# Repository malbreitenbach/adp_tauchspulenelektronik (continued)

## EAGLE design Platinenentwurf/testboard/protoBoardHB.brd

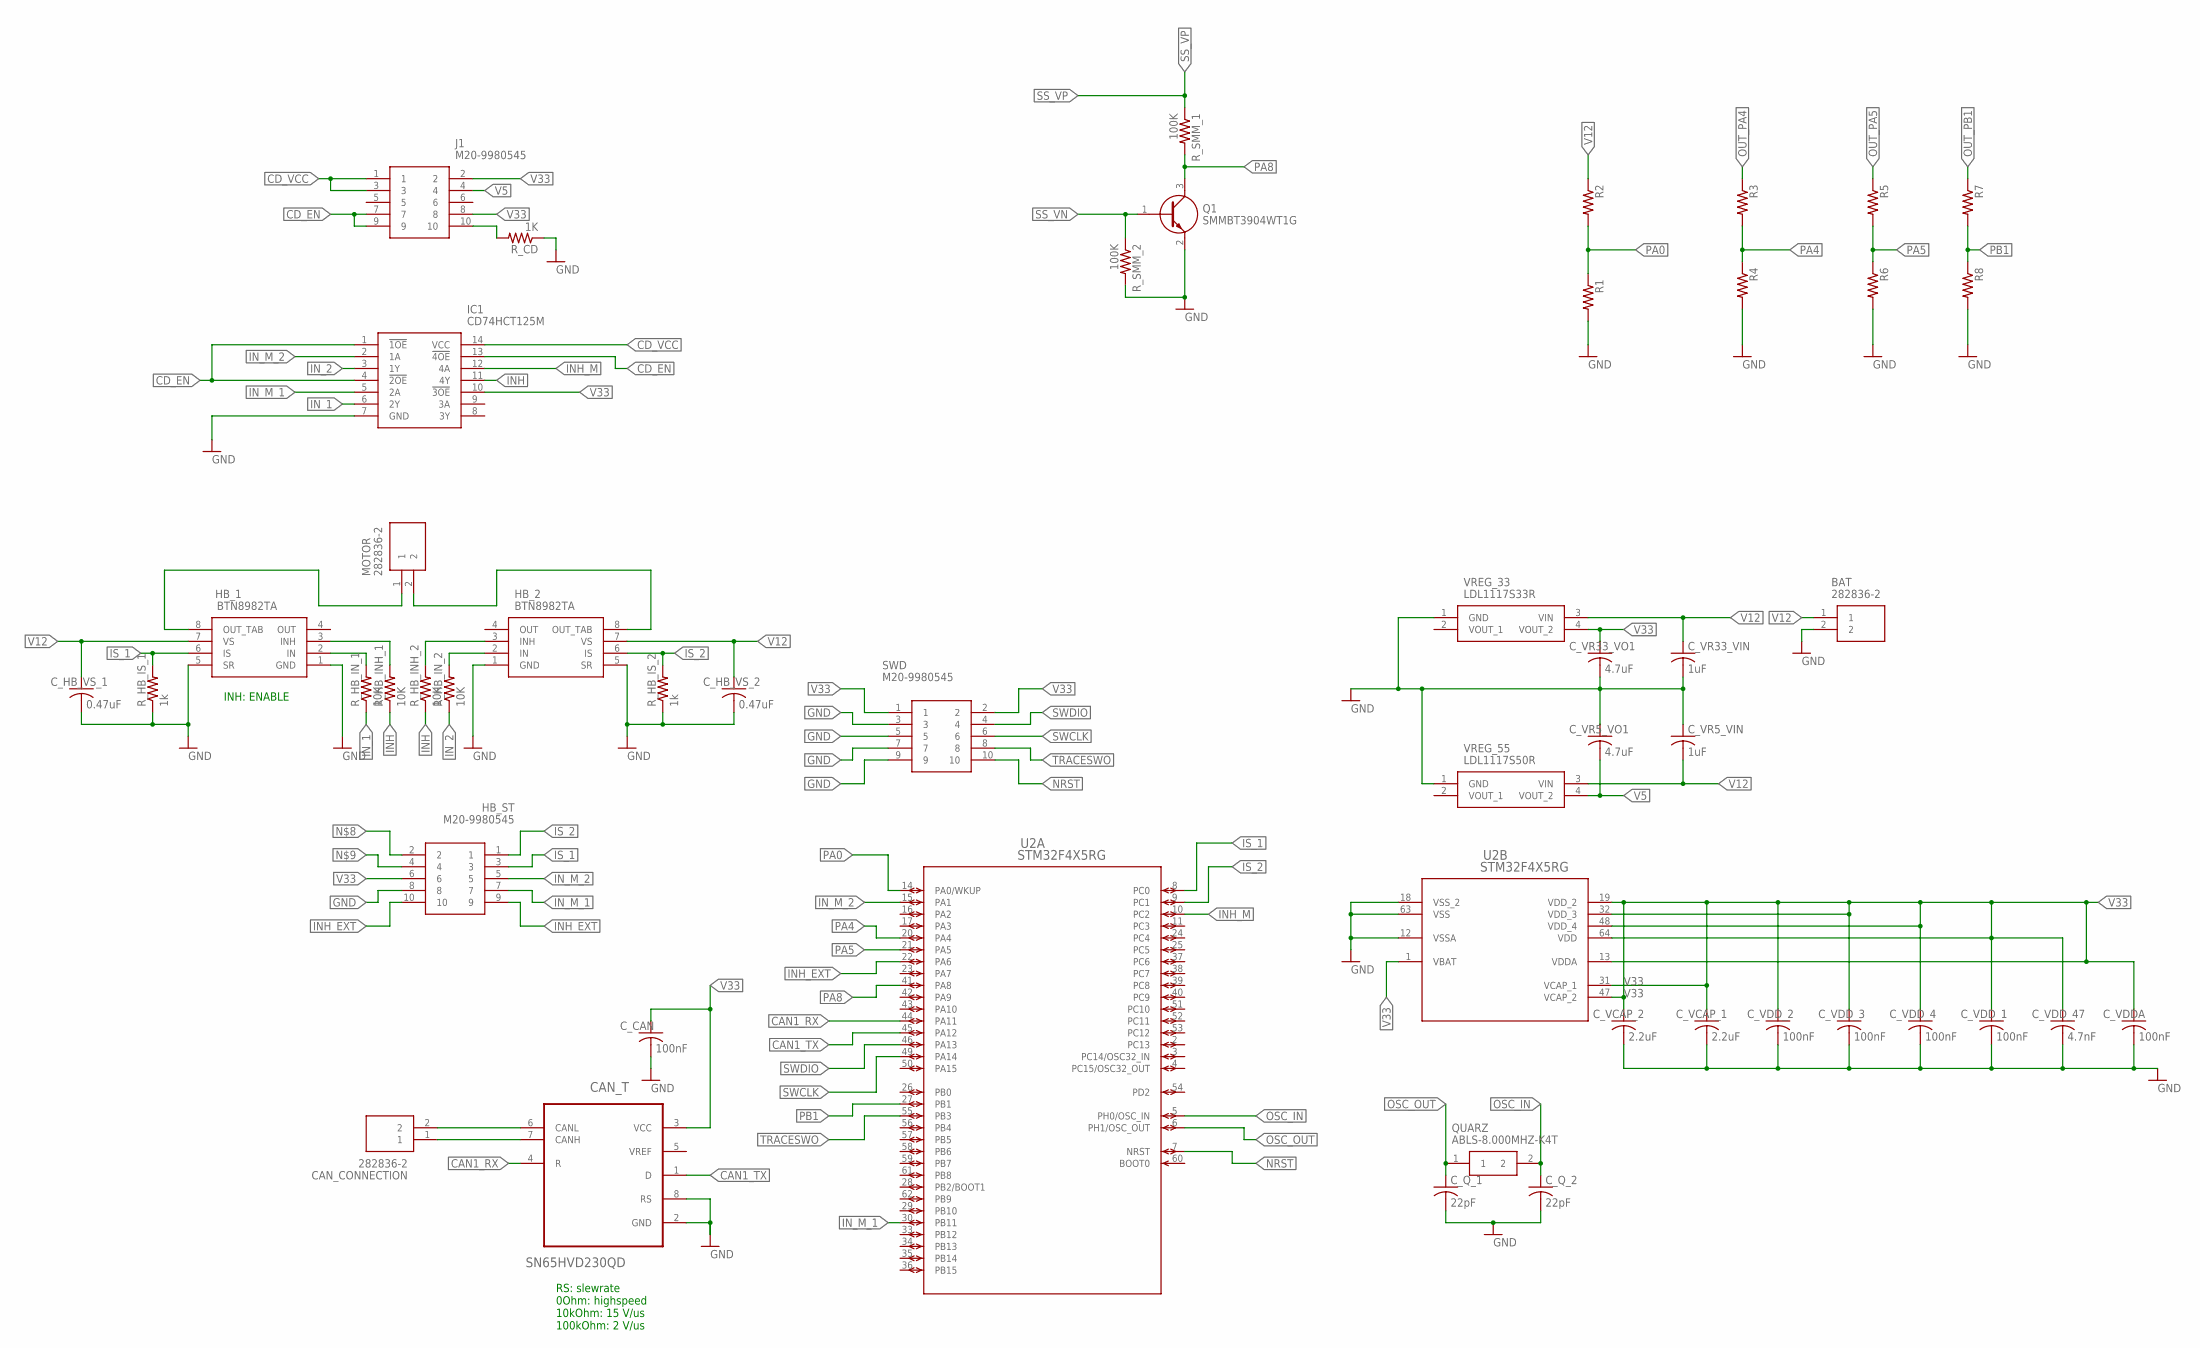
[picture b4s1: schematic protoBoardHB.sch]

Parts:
BAT: 282836-2; SHDR2W100P0X500_1X2_1000X820X1
CAN_CONNECTION: 282836-2; SHDR2W100P0X500_1X2_1000X820X1
CAN_T: SN65HVD230QD; SOIC127P600X175-8N; MPN SN65HVD230QD..
C_CAN: 100nF; C1206
C_HB_VS_1, C_HB_VS_2: 0.47uF; C1206
C_Q_1, C_Q_2: 22pF; C0805
C_VCAP_1, C_VCAP_2: 2.2uF; C1206
C_VDDA: 100nF; C1206
C_VDD_1, C_VDD_2, C_VDD_3, C_VDD_4: 100nF; C1206
C_VDD_47: 4.7nF; C1206
C_VR5_VIN, C_VR33_VIN: 1uF; C1206
C_VR5_VO1, C_VR33_VO1: 4.7uF; C1206
HB_1, HB_2: BTN8982TA; TO127P1500X440-8N
HB_ST: M20-9980545; HDRV10W80P254_2X5_1270X508X864; MPN M20-9980545
IC1: CD74HCT125M; SOIC127P600X175-14N
J1: M20-9980545; HDRV10W80P254_2X5_1270X508X864
MOTOR: 282836-2; SHDR2W100P0X500_1X2_1000X820X1
Q1: SMMBT3904WT1G; SOT65P220X100-3N
QUARZ: ABLS-8.000MHZ-K4T; ABLS-12.000MHZ-B2; MPN ABLS-8.000MHZ-K4T
R1, R2, R3, R4, R5, R6, R7, R8: R-US_R1206; R1206
R_CD: 1K; R1206
R_HB_INH_1, R_HB_INH_2: 10K; R1206
R_HB_IN_1, R_HB_IN_2: 10K; R1206
R_HB_IS_1, R_HB_IS_2: 1k; R1206
R_SMM_1, R_SMM_2: 100K; R1206
SWD: M20-9980545; HDRV10W80P254_2X5_1270X508X864; MPN M20-9980545
U2: STM32F4X5RG; LQFP64-10X10MM
VREG_33: LDL1117S33R; SOT230P700X180-4N; MPN LDL1117S33R
VREG_55: LDL1117S50R; SOT230P700X180-4N; MPN LDL1117S50R

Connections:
CAN1_RX: CAN_T.4 (R), U2.44 (PA11)
CAN1_TX: CAN_T.1 (D), U2.45 (PA12)
CANH: CAN_CONNECTION.1, CAN_T.7 (CANH)
CANL: CAN_CONNECTION.2, CAN_T.6 (CANL)
CD_EN: IC1.1 (!1OE), IC1.4 (!2OE), IC1.13 (!4OE), J1.7, J1.9
CD_VCC: IC1.14 (VCC), J1.1, J1.3
GND: BAT.2, CAN_T.2 (GND), CAN_T.8 (RS), C_CAN.2, C_HB_VS_1.2, C_HB_VS_2.2, C_Q_1.2, C_Q_2.2, C_VCAP_1.2, C_VCAP_2.2, C_VDDA.2, C_VDD_1.2, C_VDD_2.2, C_VDD_3.2, C_VDD_4.2, C_VDD_47.2, C_VR5_VIN.1, C_VR5_VO1.1, C_VR33_VIN.2, C_VR33_VO1.2, HB_1.1 (GND), HB_1.5 (SR), HB_2.1 (GND), HB_2.5 (SR), HB_ST.8, IC1.7 (GND), Q1.2 (E), R1.2, R4.2, R6.2, R8.2, R_CD.1, R_HB_IS_1.1, R_HB_IS_2.1, R_SMM_2.2, SWD.3, SWD.5, SWD.7, SWD.9, U2.12 (VSSA), U2.18 (VSS_2), U2.63 (VSS), VREG_33.1 (GND), VREG_55.1 (GND)
INH: IC1.11 (4Y), R_HB_INH_1.1, R_HB_INH_2.1
INH_EXT: HB_ST.9, HB_ST.10, U2.22 (PA6)
INH_M: IC1.12 (4A), U2.10 (PC2)
IN_1: IC1.6 (2Y), R_HB_IN_1.1
IN_2: IC1.3 (1Y), R_HB_IN_2.1
IN_M_1: HB_ST.7, IC1.5 (2A), U2.30 (PB11)
IN_M_2: HB_ST.5, IC1.2 (1A), U2.15 (PA1)
IS_1: HB_1.6 (IS), HB_ST.3, R_HB_IS_1.2, U2.8 (PC0)
IS_2: HB_2.6 (IS), HB_ST.1, R_HB_IS_2.2, U2.9 (PC1)
unnamed: J1.10, R_CD.2
unnamed: HB_1.2 (IN), R_HB_IN_1.2
unnamed: HB_1.3 (INH), R_HB_INH_1.2
unnamed: HB_2.2 (IN), R_HB_IN_2.2
unnamed: HB_2.3 (INH), R_HB_INH_2.2
NRST: SWD.10, U2.7 (NRST)
OSC_IN: C_Q_2.1, QUARZ.2, U2.5 (PH0/OSC_IN)
OSC_OUT: C_Q_1.1, QUARZ.1, U2.6 (PH1/OSC_OUT)
OUT_PA4: R3.1
OUT_PA5: R5.1
OUT_PB1: R7.1
PA0: R1.1, R2.2, U2.14 (PA0/WKUP)
PA4: R3.2, R4.1, U2.20 (PA4)
PA5: R5.2, R6.1, U2.21 (PA5)
PA8: Q1.3 (C), R_SMM_1.2, U2.41 (PA8)
PB1: R7.2, R8.1, U2.27 (PB1)
SS_VN: Q1.1 (B), R_SMM_2.1
SS_VP: R_SMM_1.1
SWCLK: SWD.6, U2.49 (PA14)
SWDIO: SWD.4, U2.46 (PA13)
TRACESWO: SWD.8, U2.55 (PB3)
V5: C_VR5_VO1.2, J1.4, VREG_55.4 (VOUT_2)
V12: BAT.1, C_HB_VS_1.1, C_HB_VS_2.1, C_VR5_VIN.2, C_VR33_VIN.1, HB_1.7 (VS), HB_2.7 (VS), R2.1, VREG_33.3 (VIN), VREG_55.3 (VIN)
V33: CAN_T.3 (VCC), C_CAN.1, C_VCAP_1.1, C_VCAP_2.1, C_VDDA.1, C_VDD_1.1, C_VDD_2.1, C_VDD_3.1, C_VDD_4.1, C_VDD_47.1, C_VR33_VO1.1, HB_ST.6, IC1.10 (!3OE), J1.2, J1.8, SWD.1, SWD.2, U2.1 (VBAT), U2.13 (VDDA), U2.19 (VDD_2), U2.31 (VCAP_1), U2.32 (VDD_3), U2.47 (VCAP_2), U2.48 (VDD_4), U2.64 (VDD), VREG_33.4 (VOUT_2)
V_MOT_MIN: HB_2.8 (OUT_TAB), MOTOR.2
V_MOT_PL: HB_1.8 (OUT_TAB), MOTOR.1

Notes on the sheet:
RS: slewrate 0Ohm: highspeed 10kOhm: 15 V/us 100kOhm: 2 V/us
INH: ENABLE

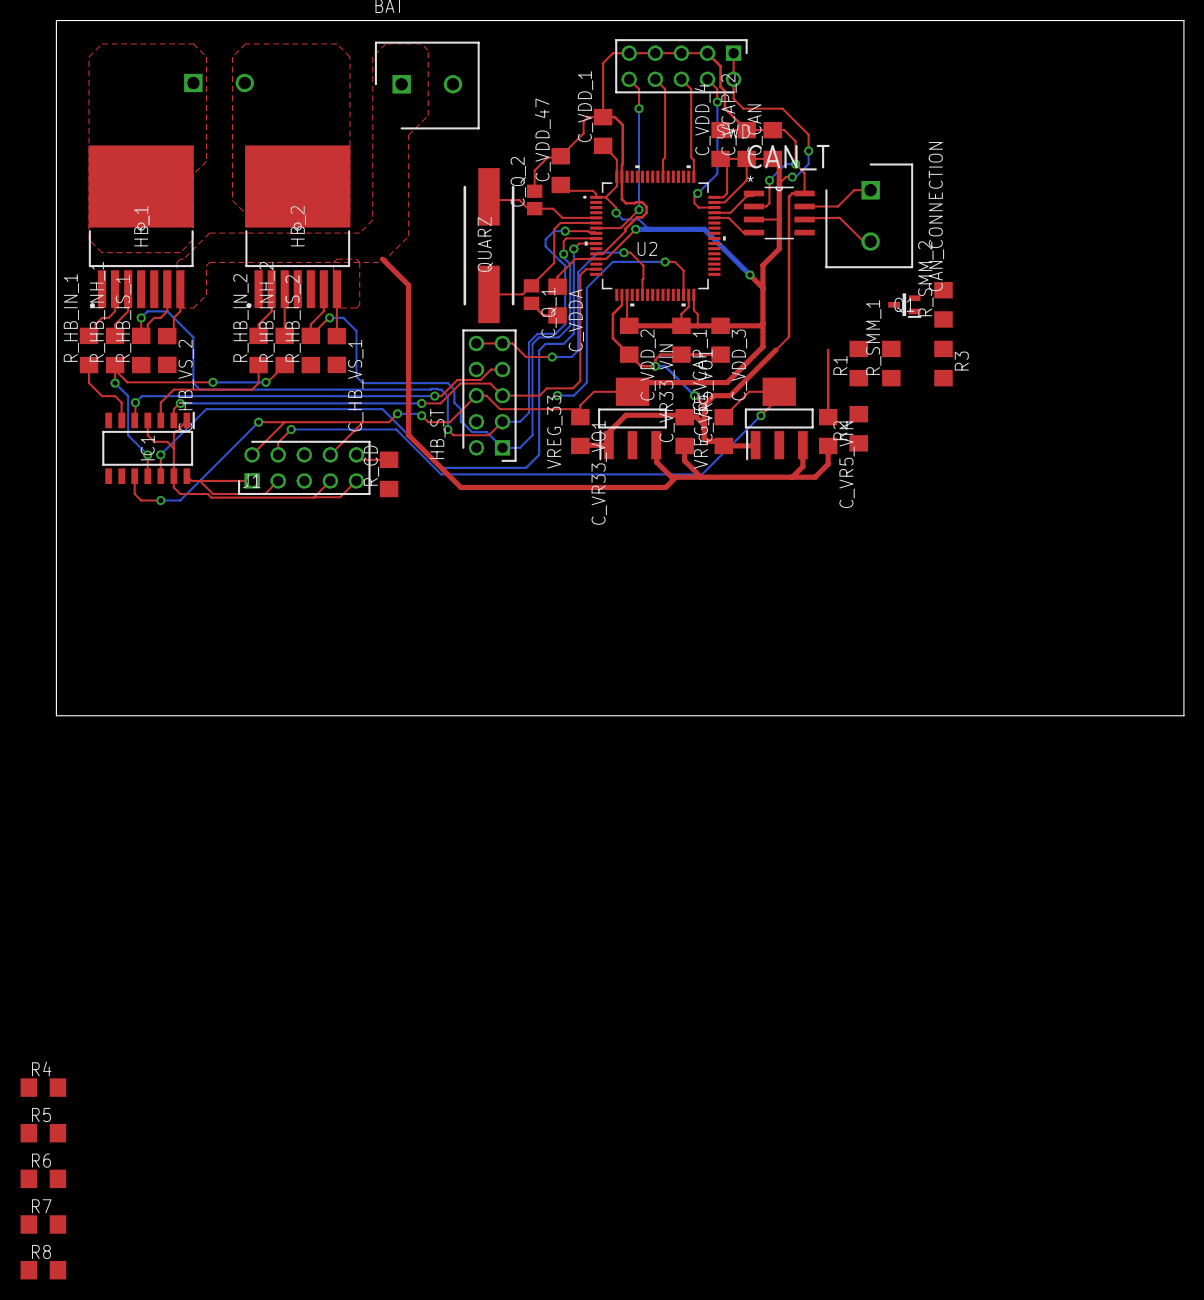
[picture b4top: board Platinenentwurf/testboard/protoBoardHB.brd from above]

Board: 2 copper layers, 109.8 x 67.7 mm, 49 parts (1 on the bottom side), 38 nets.

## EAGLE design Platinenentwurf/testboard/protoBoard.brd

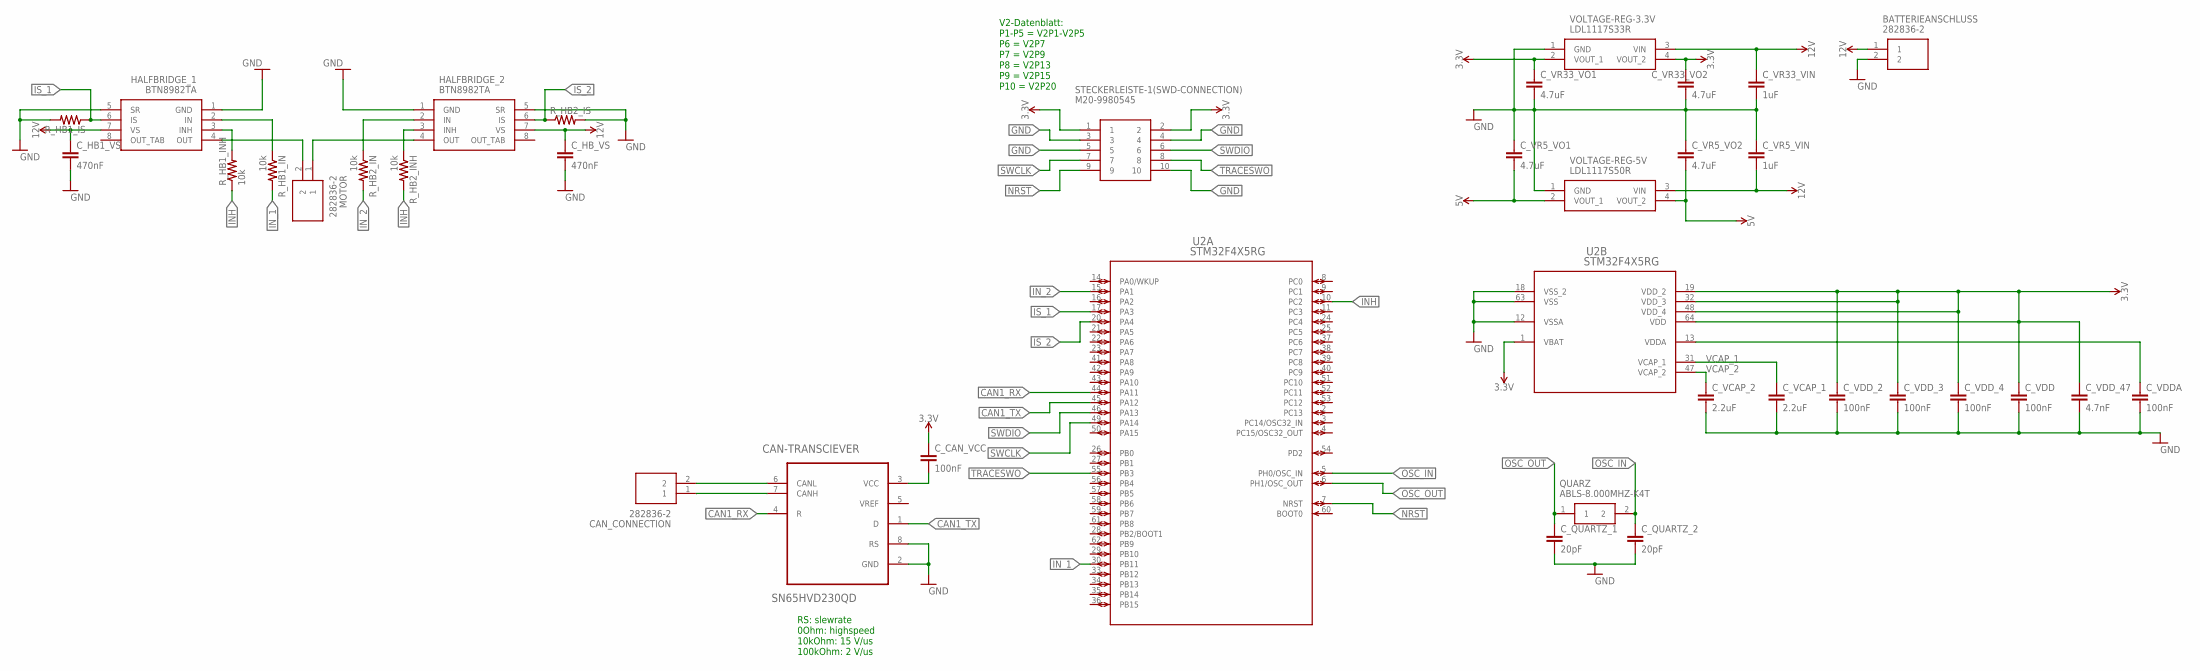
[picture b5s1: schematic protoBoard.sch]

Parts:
BATTERIEANSCHLUSS: 282836-2; SHDR2W100P0X500_1X2_1000X820X1
CAN-TRANSCIEVER: SN65HVD230QD; SOIC127P600X175-8N; MPN SN65HVD230QD..
CAN_CONNECTION: 282836-2; SHDR2W100P0X500_1X2_1000X820X1
C_CAN_VCC: 100nF; C2.5-6
C_HB1_VS: 470nF; C2.5-6
C_HB_VS: 470nF; C2.5-6
C_QUARTZ_1, C_QUARTZ_2: 20pF; C2.5-6
C_VCAP_1, C_VCAP_2: 2.2uF; C2.5-6
C_VDD: 100nF; C2.5-6
C_VDDA: 100nF; C2.5-6
C_VDD_2, C_VDD_3, C_VDD_4: 100nF; C2.5-6
C_VDD_47: 4.7nF; C2.5-6
C_VR5_VIN, C_VR33_VIN: 1uF; C2.5-6
C_VR5_VO1, C_VR5_VO2, C_VR33_VO1, C_VR33_VO2: 4.7uF; C2.5-6
HALFBRIDGE_1, HALFBRIDGE_2: BTN8982TA; TO127P1500X440-8N
MOTOR: 282836-2; SHDR2W100P0X500_1X2_1000X820X1
QUARZ: ABLS-8.000MHZ-K4T; ABLS-12.000MHZ-B2; MPN ABLS-8.000MHZ-K4T
R_HB1_IN, R_HB1_INH, R_HB2_IN, R_HB2_INH: 10k; 0204/7
R_HB1_IS, R_HB2_IS: R-US_0204/7; 0204/7
STECKERLEISTE-1(SWD-CONNECTION): M20-9980545; HDRV10W80P254_2X5_1270X508X864; MPN M20-9980545
U2: STM32F4X5RG; LQFP64-10X10MM
VOLTAGE-REG-3.3V: LDL1117S33R; SOT230P700X180-4N; MPN LDL1117S33R
VOLTAGE-REG-5V: LDL1117S50R; SOT230P700X180-4N; MPN LDL1117S50R

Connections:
12V: BATTERIEANSCHLUSS.1, C_HB1_VS.1, C_HB_VS.1, C_VR5_VIN.2, C_VR33_VIN.1, HALFBRIDGE_1.7 (VS), HALFBRIDGE_2.7 (VS), VOLTAGE-REG-3.3V.3 (VIN), VOLTAGE-REG-5V.3 (VIN)
CAN1_RX: CAN-TRANSCIEVER.4 (R), U2.44 (PA11)
CAN1_TX: CAN-TRANSCIEVER.1 (D), U2.45 (PA12)
GND: BATTERIEANSCHLUSS.2, CAN-TRANSCIEVER.2 (GND), CAN-TRANSCIEVER.8 (RS), C_HB1_VS.2, C_HB_VS.2, C_QUARTZ_1.2, C_QUARTZ_2.2, C_VCAP_1.2, C_VCAP_2.2, C_VDD.2, C_VDDA.2, C_VDD_2.2, C_VDD_3.2, C_VDD_4.2, C_VDD_47.2, C_VR5_VIN.1, C_VR5_VO1.1, C_VR5_VO2.1, C_VR33_VIN.2, C_VR33_VO1.2, C_VR33_VO2.2, HALFBRIDGE_1.1 (GND), HALFBRIDGE_1.5 (SR), HALFBRIDGE_2.1 (GND), HALFBRIDGE_2.5 (SR), R_HB1_IS.2, R_HB2_IS.2, STECKERLEISTE-1(SWD-CONNECTION).3, STECKERLEISTE-1(SWD-CONNECTION).4, STECKERLEISTE-1(SWD-CONNECTION).5, STECKERLEISTE-1(SWD-CONNECTION).10, U2.12 (VSSA), U2.18 (VSS_2), U2.63 (VSS), VOLTAGE-REG-3.3V.1 (GND), VOLTAGE-REG-5V.1 (GND)
INH: R_HB1_INH.1, R_HB2_INH.2, U2.10 (PC2)
IN_1: R_HB1_IN.2, U2.30 (PB11)
IN_2: R_HB2_IN.2, U2.15 (PA1)
IS_1: HALFBRIDGE_1.6 (IS), R_HB1_IS.1, U2.17 (PA3)
IS_2: HALFBRIDGE_2.6 (IS), R_HB2_IS.1, U2.20 (PA4)
unnamed: C_VDDA.1, U2.13 (VDDA)
unnamed: CAN-TRANSCIEVER.3 (VCC), C_CAN_VCC.2
unnamed: CAN-TRANSCIEVER.6 (CANL), CAN_CONNECTION.2
unnamed: CAN-TRANSCIEVER.7 (CANH), CAN_CONNECTION.1
unnamed: HALFBRIDGE_1.4 (OUT), MOTOR.2
unnamed: HALFBRIDGE_2.4 (OUT), MOTOR.1
unnamed: HALFBRIDGE_1.3 (INH), R_HB1_INH.2
unnamed: HALFBRIDGE_2.3 (INH), R_HB2_INH.1
unnamed: HALFBRIDGE_1.2 (IN), R_HB1_IN.1
unnamed: HALFBRIDGE_2.2 (IN), R_HB2_IN.1
NRST: STECKERLEISTE-1(SWD-CONNECTION).9, U2.7 (NRST)
OSC_IN: C_QUARTZ_2.1, QUARZ.2, U2.5 (PH0/OSC_IN)
OSC_OUT: C_QUARTZ_1.1, QUARZ.1, U2.6 (PH1/OSC_OUT)
SWCLK: STECKERLEISTE-1(SWD-CONNECTION).7, U2.49 (PA14)
SWDIO: STECKERLEISTE-1(SWD-CONNECTION).6, U2.46 (PA13)
TRACESWO: STECKERLEISTE-1(SWD-CONNECTION).8, U2.55 (PB3)
VCAP_1: C_VCAP_1.1, U2.31 (VCAP_1)
VCAP_2: C_VCAP_2.1, U2.47 (VCAP_2)
VCC: C_CAN_VCC.1, C_VDD.1, C_VDD_2.1, C_VDD_3.1, C_VDD_4.1, C_VDD_47.1, C_VR5_VO1.2, C_VR5_VO2.2, C_VR33_VO1.1, C_VR33_VO2.1, STECKERLEISTE-1(SWD-CONNECTION).1, STECKERLEISTE-1(SWD-CONNECTION).2, U2.1 (VBAT), U2.19 (VDD_2), U2.32 (VDD_3), U2.48 (VDD_4), U2.64 (VDD), VOLTAGE-REG-3.3V.2 (VOUT_1), VOLTAGE-REG-3.3V.4 (VOUT_2), VOLTAGE-REG-5V.2 (VOUT_1), VOLTAGE-REG-5V.4 (VOUT_2)

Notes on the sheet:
RS: slewrate 0Ohm: highspeed 10kOhm: 15 V/us 100kOhm: 2 V/us
V2-Datenblatt: P1-P5 = V2P1-V2P5 P6 = V2P7 P7 = V2P9 P8 = V2P13 P9 = V2P15 P10 = V2P20

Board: 2 copper layers, 36 parts (0 on the bottom side), 28 nets, no tracks yet.

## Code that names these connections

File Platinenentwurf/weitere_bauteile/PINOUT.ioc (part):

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Mcu.Name=STM32F405RGTx
Mcu.Package=LQFP64
Mcu.UserName=STM32F405RGTx
PA0-WKUP.Signal=ADCx_IN0
PA1.Signal=ADCx_IN1
PA11.Mode=Master
PA11.Signal=CAN1_RX
PA12.Mode=Master
PA12.Signal=CAN1_TX
PA13.Mode=Serial_Wire
PA13.Signal=SYS_JTMS-SWDIO
PA14.Mode=Serial_Wire
PA14.Signal=SYS_JTCK-SWCLK
PA2.Mode=Asynchronous
PA2.Signal=USART2_TX
PA3.Mode=Asynchronous
PA3.Signal=USART2_RX
PB0.Signal=ADCx_IN8
PB1.Signal=ADCx_IN9
PB10.Signal=S_TIM2_CH3
PB11.Signal=S_TIM2_CH4
PB3.Signal=SYS_JTDO-SWO
PC2.Signal=ADCx_IN12
PC3.Signal=ADCx_IN13
PC4.Signal=GPIO_Output
PC5.Signal=ADCx_IN15
PH0-OSC_IN.Mode=HSE-External-Oscillator
PH0-OSC_IN.Signal=RCC_OSC_IN
PH1-OSC_OUT.Mode=HSE-External-Oscillator
PH1-OSC_OUT.Signal=RCC_OSC_OUT
RCC.HSE_VALUE=25000000
RCC.SYSCLKFreq_VALUE=16000000
board=custom

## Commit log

2018-11-22 Weitere wichtige Änderung
2018-11-22 Initial Demo Project
2018-11-22 Super wichtige Neuerung!
2018-12-05 Probeweise Änderung.
2018-12-05 Test Text Datei
2018-12-05 Update Paper.txt
    Erwiederung
2018-12-05 Initial Push für Literatur Datei
2018-12-17 Bestelliste fuer Prototypen erstellt.
2018-12-17 Ergaenzung zu Bestelliste
2018-12-17 Befehle für Git
2018-12-17 Informationsblatt zu ADCs
2018-12-17 Datenblaetter hinzugefuegt
2018-12-17 Weitere Literatur hinzugefuegt
2018-12-17 Vorangegangene ADPs
2018-12-17 Notizen zum Aktor hinzugefuegt
2018-12-19 Anforderungsliste erstellt
2018-12-19 Kleine Rechtschreibanpassungen
2018-12-19 commit funktioniert (vllt nur bei mir nur mit zus. -a)
2018-12-19 Anforderungsliste angepasst nach Treffen mit Daniel
2018-12-19 Bestelliste
2018-12-19 Bestellliste vervollständigt
2019-01-17 Datenblatt für Entwicklungsboard
2019-01-29 Datenblattt discovery shield, Bestellung Minimalbesschaltung added
2019-01-29 Aenderung Bestellliste
2019-02-01 aenderung bestellliste minimalbeschaltung
2019-02-15 Platinenentwurf added
2019-02-17 ProtoBoard update
2019-02-18 weitere Bauteile
2019-02-18 Platinenentwurf bearbeitet
2019-02-18 Platinenzeugs + Boardbilder zur ueberpruefung
2019-02-18 Platinenentwurf: kleines Update
2019-02-18 Datenblätter+ neue Bestellliste
2019-02-19 änderungen Platine + Bestellliste
2019-02-19 Bauteile für Platine hinzugefügt
2019-02-19 kleine Ergänzung
2019-02-19 Aktualisierung
2019-02-19 update Platine
2019-02-19 Platinenupdate
2019-02-20 Add files via upload
    Sorry, musste es neu hochladen.
    Johanna
2019-02-20 Bestellistenupdate
2019-02-20 Platinenupdate auf 0.7um Kupfer
2019-02-20 lötpaste hinzugefügt in bestellliste
2019-03-01 Bauteilzuweisungen fuer loeten
2019-03-02 Johannes: Erstellen LatexVorlage
2019-03-02 nix geändert
2019-03-04 nachbestllliste
2019-03-04 Sicherung und Ringkabelschuhe hinzugefügt
2019-03-07 Neue Platine
2019-03-07 Aktualisierung nach Telefonat
2019-03-07 Platinenänderung
2019-03-07 Kapitel Prüfstand
2019-03-07 LaTeX Kapitel Prüfstand hinzugefügt
2019-03-07 Latex: Johanna geholfen
2019-03-07 Ausarbeitung vorheriges ADP und Bilder hinzugefügt
2019-03-07 Platine
2019-03-07 Ausarbeitung Kapitel 2
2019-03-07 LaTeX Einleitung
2019-03-07 CAD Bilder
2019-03-07 Neue Bauteile
2019-03-07 Platinenentwurf
2019-03-07 Korrektur Tabelle Latex
2019-03-08 datenblatt halfbridge
2019-03-08 Inventarliste added
2019-03-08 Ausarbeitung
2019-03-08 Platinenzeug
2019-03-10 Buffer Datenblatt
2019-03-10 Leistungstabelle
2019-03-10 Bestellliste aktualisiert
2019-03-10 inventarliste aktualiesiert
2019-03-11 Platinenzeugs
2019-03-11 Bestellliste
2019-03-13 bestellliste aktualiesiert
2019-03-21 Kostenüberschlag
2019-03-22 Board
2019-03-22 Platinenkosten
2019-03-25 Bestellung Backup
2019-03-26 Bilder
2019-03-26 mergen
2019-03-26 Hauptstruktur Latex
2019-03-26 Bilder Prototyp
2019-03-26 Weiterentwicklung
2019-03-26 Kapitel 3 letzte Versoin
2019-03-26 Literatur
2019-03-27 aktuelle Ausarbeitung
2019-03-27 Bild Malte
2019-03-27 Stecker
2019-03-27 Kapitel 7
2019-03-27 Abstract
2019-03-28 Fazit
2019-03-31 Daniels sachen korriegiert hauptsächlich kap 4
2019-03-31 Gitignore
2019-03-31 Software Kapitel verbessert
2019-03-31 Utrack files
2019-03-31 neuer Latex Ordner
2019-03-31 neuer Latex Ordner2
2019-03-31 Grafen korrigiert
2019-03-31 kap 5,6,7,8 korriegiert
2019-04-01 Korrekturen Kap6
2019-04-01 ´Bildeinschüber korriegiert
2019-04-01 Kap6
    git commit -m Kap6
2019-04-01 Kapitel 2
2019-04-01 Kapitel2
2019-04-01 Akronymverzeichnis
2019-04-01 Kapitel 3
2019-04-01 ´johanna nervt
2019-04-01 Tabellen
2019-04-01 Tabelle
2019-04-01 Ausbesserung Abbildung
2019-04-01 ´maltes grafiken
2019-04-01 meine Aenderungen
2019-04-02 Verbesserungen Kapitel 2
2019-04-02 ´kap 3 jonas
2019-04-02 kap6
2019-04-02 ´ jonas
2019-04-02 Anhang
2019-04-02 ´ jonas library
2019-04-02 Einleitung
2019-04-02 Kapitel 8
2019-04-02 Akronym
2019-10-24 Finales Platinenlayout
